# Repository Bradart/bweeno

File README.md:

# bweeno

This is a dumping ground for all of my useful Arduino sketches. There probably won't be anything revolutionary here but I'll be god damned if something useful doesn't pop up in here ocassionally. I also try to add wiring diagrams and such when I can. Neato Burrito.

boop

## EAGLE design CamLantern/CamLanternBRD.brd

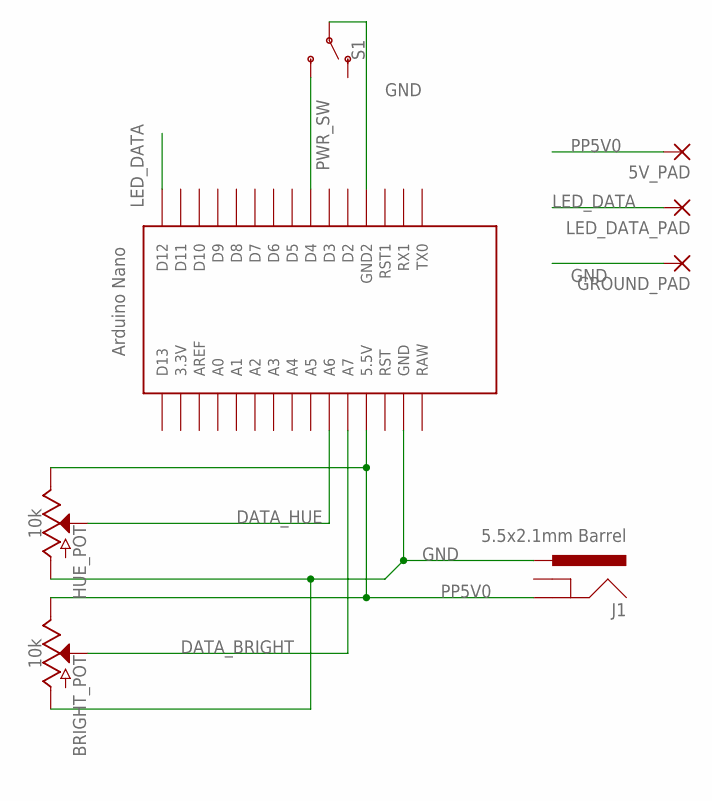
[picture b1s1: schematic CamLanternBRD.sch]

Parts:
5V_PAD: 1,6/0,9
BRIGHT_POT: 10k; POT-PTH-ALPS-KIT
GROUND_PAD: 1,6/0,9
HUE_POT: 10k; POT-PTH-ALPS-KIT
J1: 5.5x2.1mm Barrel; POWER_JACK_SMD
LED_DATA_PAD: 1,6/0,9
S1: SWITCH-SPDT-PTH-11.6X4.0MM; SWITCH_SPDT_PTH_11.6X4.0MM
U$2: NANO

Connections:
DATA_BRIGHT: BRIGHT_POT.P$2 (S), U$2.A7
DATA_HUE: HUE_POT.P$2 (S), U$2.A6
GND: BRIGHT_POT.P$3 (A), GROUND_PAD.1, HUE_POT.P$3 (A), J1.VIN0 (PWR), S1.2, U$2.GND, U$2.GND1 (GND2)
LED_DATA: LED_DATA_PAD.1, U$2.D12
PP5V0: 5V_PAD.1, BRIGHT_POT.P$1 (E), HUE_POT.P$1 (E), J1.P$4 (GND), U$2.5V (5.5V)
PWR_SW: S1.3 (S), U$2.D4

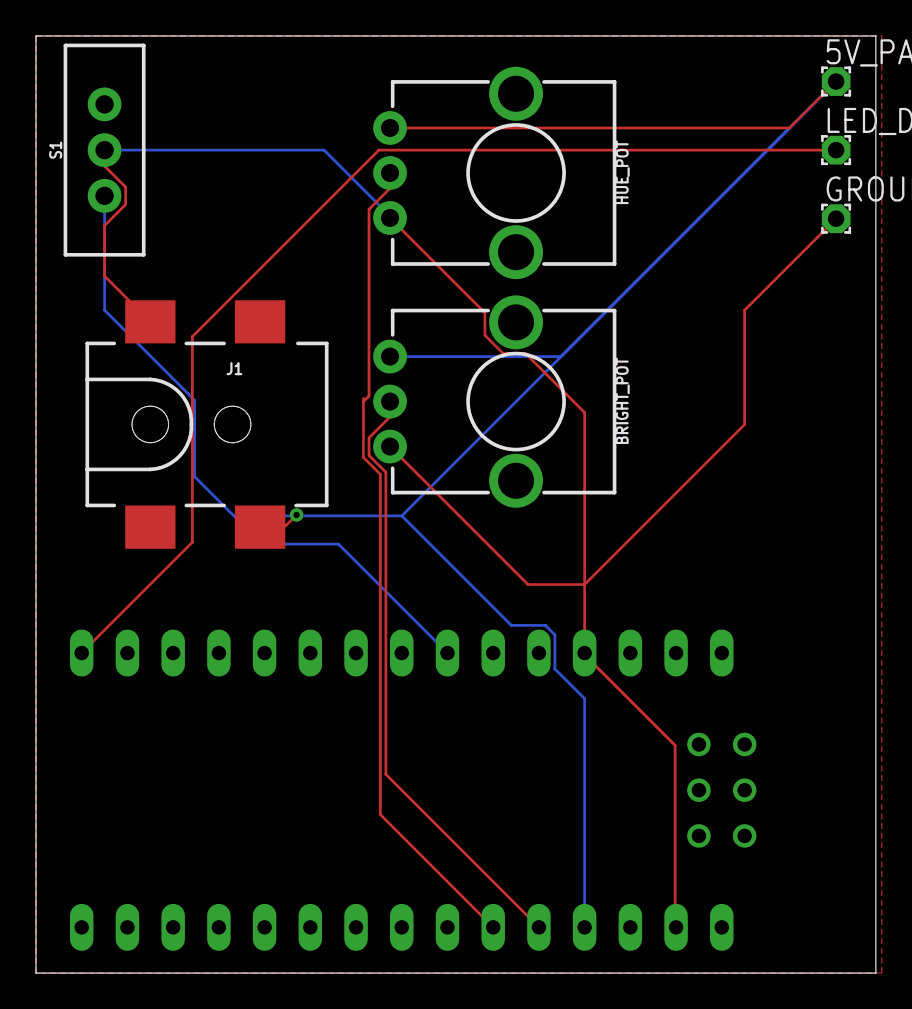
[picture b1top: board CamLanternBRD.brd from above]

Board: 2 copper layers, 46.7 x 52.1 mm, 8 parts (0 on the bottom side), 6 nets.

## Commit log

2018-04-16 adding the actual sketches
2018-04-16 added toggle switch test
2018-04-16 Adding comments to the toggle code. It's pretty dope
2018-04-16 wtf is wrong with this god damn arduino sketch
2018-04-16 trying to fix these fucking directories
2018-04-17 uploading drawings and skeleton for rgb analog controller
2018-04-17 adding actual code to the RGB thing or whatever
2018-04-17 adding better comments
2018-04-18 don't ask
2018-04-18 ughhhhhh
2018-04-18 Added indicator lights and serial output for testing purposes. Also changes some pin address because fuck it
2018-04-18 added example code for addressable LEDs
2018-04-18 whoa boy a whole bunch of things. Added two new sketches messing with addressable LED strips. Will upload diagrams later
2018-04-18 made some minor changes to the speed calculations
2018-04-19 streamlined some analog->pwm code. It's as sexy as it sounds.
2018-04-19 had to delete an errant file
2018-04-19 added skeleton for adressable LEDs
2018-04-19 added some diagrams and cleaned up some code. Still need to properly comment some things
2018-04-20 updated diagrams
2018-04-20 fixed the value mapping because I'm stupid
2018-04-24 adding ir receiver raw read sketch
2018-04-26 adding some things
2018-04-26 Going to change some code to try and smooth the color transitions
2018-04-26 FINALLY FIXED THE COLOR TRANSITIONS! Also, added a pure white mode for added illumination
2018-05-03 adding cameron's lantern code. Will add diagrams shortly because I made a controller board for this one.
2018-05-03 updated readme a bit. Added cuss words because SHITFUCK
2018-05-03 removing some bullshit
2018-05-03 adding those diagrams. Eagle board coming soon
2018-05-03 Fixed friting's dumbass pin layout-related errors in the images.
2018-05-03 OH MY GOD FRITZING AND ITS FUCKING BROKEN ROUTING ALGORITHM
2018-05-03 Board files
    control board PCB files. Ready to send to printer.
2018-05-03 omfg
2018-05-06 Added a rainbow oscillation mode
2018-05-10 Adding to README
2018-05-22 added ATtiny sketch
    becuase fuck yes life is awesome
2018-05-22 cylonify
    cylon
2018-05-23 added 2 pot thing
2018-06-01 added tac toggles
2018-06-01 Pointer update
    Converted all the function variable set statements and replaced them with pointers in the function. Also converted all functions to void saving an ASS TON of memory on the MCU
2018-06-11 added rainbow code and shit
2018-06-11 commented code
    added comments, rearranged functions layout a bit. Will be adding debouncing in future revision
2018-06-12 Creation of bias light project
    untested on actual device.
2018-06-16 added rainbow mode
2018-06-16 Fixed rainbow termination error
    Fixe the problem that caused rainbow mode to be impossible to exit
2018-06-16 fixed a flickering issue
2018-06-24 --
    \\'[T] //
2018-07-09 boop
2018-07-11 new lightning idea

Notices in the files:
parts and their libraries:
SparkFun-Resistors: Licensing: Creative Commons ShareAlike 4.0 International - https://creativecommons.org/licenses/by-sa/4.0
